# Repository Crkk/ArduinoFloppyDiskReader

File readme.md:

# Arduino Powered Amiga Floppy Disk Reader and Writer
Created by Robert Smith @RobSmithDev

Hardware design added by @Crkk

# What is it?
This project uses an Arduino to interface with a floppy disk drive and communicate with a PC in order to recover the data from Amiga formatted AmigaDOS disks.
It also allows you to write a backed up ADF file back onto a floppy disk!

# ArduinoFloppyReader
This Visual Studio 2017 project contains two applications, a command line, and a Windows dialog based application

# FloppyDriverController.sketch
This is the Ardunio source code/sketch

# AVR Firmware
If you want to use the AVR directly instead of within the Arduino environment, then jump to [https://github.com/jtsiomb/usbamigafloppy] where John Tsiombikas has ported the code.

# Help and Instructions 
For further details including how to wire this up please visit [http://amiga.robsmithdev.co.uk]

# Whats changed?
V2.2 Fixed 99% of checksum errors when writing by erasing the track first
V2.1 Diagnostics and potential write bug fixed
V2.0 Disk reading has been vastly improved and you can now also write disks!
V1.0 Initial release, can read disks fairly well

# Licence
This entire project is available under the GNU General Public License v3 licence.  See licence.txt for more details.

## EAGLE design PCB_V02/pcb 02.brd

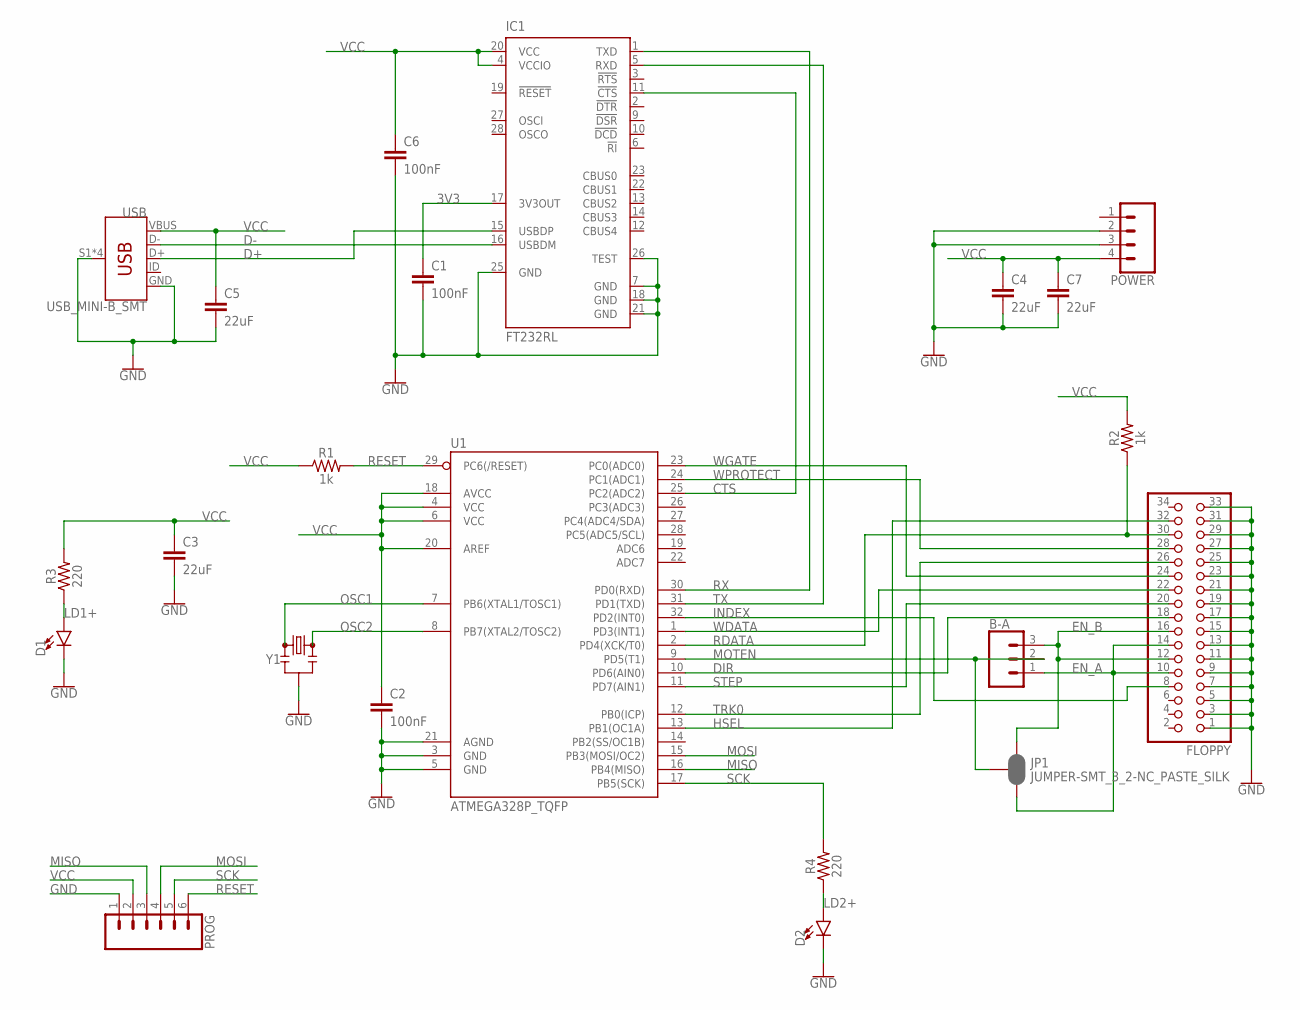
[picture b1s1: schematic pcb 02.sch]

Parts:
B-A: CONN_03; 1X03
C1, C2, C6: 100nF; 0603
C3, C4, C5, C7: 22uF; C0805
D1, D2: LED5MM; LED_5MM
FLOPPY: PINHD-2X17_2.54-90°; 2X17/90
IC1: FT232RL; SSOP28
JP1: JUMPER-SMT_3_2-NC_PASTE_SILK; SMT-JUMPER_3_2-NC_PASTE_SILK
POWER: CONN_04; 1X04
PROG: CONN_06SILK_FEMALE_PTH; 1X06
R1, R2: 1k; 0603
R3, R4: 220; 0603
U1: ATMEGA328P_TQFP; TQFP32-08
USB: USB_MINI-B_SMT; USB-MINIB
Y1: RESONATORSMD-3.2X1.3; RESONATOR-SMD-3.2X1.3

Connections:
3V3: C1.1, IC1.17 (3V3OUT)
CTS: IC1.11 (!CTS), U1.25 (PC2(ADC2))
D+: IC1.15 (USBDP), USB.D+
D-: IC1.16 (USBDM), USB.D-
DIR: FLOPPY.18, U1.10 (PD6(AIN0))
EN_A: B-A.1, FLOPPY.10, FLOPPY.14, JP1.3
EN_B: B-A.3, FLOPPY.12, FLOPPY.16, JP1.1
GND: C1.2, C2.2, C3.2, C4.2, C5.2, C6.2, C7.2, D1.K (C), D2.K (C), FLOPPY.1, FLOPPY.3, FLOPPY.5, FLOPPY.7, FLOPPY.9, FLOPPY.11, FLOPPY.13, FLOPPY.15, FLOPPY.17, FLOPPY.19, FLOPPY.21, FLOPPY.23, FLOPPY.25, FLOPPY.27, FLOPPY.29, FLOPPY.31, FLOPPY.33, IC1.7 (GND), IC1.18 (GND), IC1.21 (GND), IC1.25 (GND), IC1.26 (TEST), POWER.2, POWER.3, PROG.1, U1.3 (GND), U1.5 (GND), U1.21 (AGND), USB.GND, USB.S1 (SHIELD), USB.S2 (SHIELD), USB.S3 (SHIELD), USB.S4 (SHIELD), Y1.2
HSEL: FLOPPY.32, U1.13 (PB1(OC1A))
INDEX: FLOPPY.8, U1.32 (PD2(INT0))
LD1+: D1.A, R3.1
LD2+: D2.A, R4.1
MISO: PROG.3, U1.16 (PB4(MISO))
MOSI: PROG.4, U1.15 (PB3(MOSI/OC2))
MOTEN: B-A.2, JP1.2, U1.9 (PD5(T1))
OSC1: U1.7 (PB6(XTAL1/TOSC1)), Y1.1
OSC2: U1.8 (PB7(XTAL2/TOSC2)), Y1.3
RDATA: FLOPPY.30, R2.1, U1.2 (PD4(XCK/T0))
RESET: PROG.6, R1.2, U1.29 (PC6(/RESET))
RX: IC1.1 (TXD), U1.30 (PD0(RXD))
SCK: PROG.5, R4.2, U1.17 (PB5(SCK))
STEP: FLOPPY.20, U1.11 (PD7(AIN1))
TRK0: FLOPPY.26, U1.12 (PB0(ICP))
TX: IC1.5 (RXD), U1.31 (PD1(TXD))
VCC: C2.1, C3.1, C4.1, C5.1, C6.1, C7.1, IC1.4 (VCCIO), IC1.20 (VCC), POWER.4, PROG.2, R1.1, R2.2, R3.2, U1.4 (VCC), U1.6 (VCC), U1.18 (AVCC), U1.20 (AREF), USB.VBUS
WDATA: FLOPPY.22, U1.1 (PD3(INT1))
WGATE: FLOPPY.24, U1.23 (PC0(ADC0))
WPROTECT: FLOPPY.28, U1.24 (PC1(ADC1))

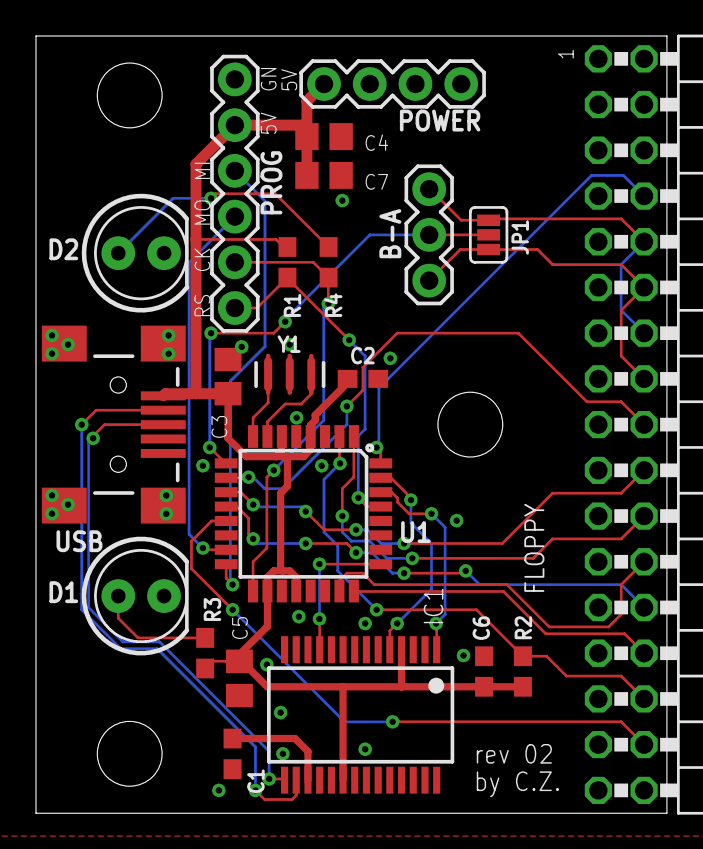
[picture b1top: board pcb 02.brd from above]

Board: 2 copper layers, 35.1 x 43.2 mm, 22 parts (0 on the bottom side), 28 nets.

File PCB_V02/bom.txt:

100 nF 50V	C1, C2, C6	0603
1 kOhm		R1, R2		0603
220 Ohm		R3, R4		0603
22 uF 25V	C3, C4, C5, C7	0805
ATMEGA328P	U1		TQFP32
FT232RL		IC1		SSOP28

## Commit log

2020-10-22 Update ArduinoInterface.cpp
    typo fix
2021-06-03 Rename pcb 000.brd to pcb 06.brd
2021-06-03 Rename pcb 000.sch to pcb 06.sch

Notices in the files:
parts and their libraries:
SparkFun-IC-Microcontroller: Licensing: Creative Commons ShareAlike 4.0 International - https://creativecommons.org/licenses/by-sa/4.0
